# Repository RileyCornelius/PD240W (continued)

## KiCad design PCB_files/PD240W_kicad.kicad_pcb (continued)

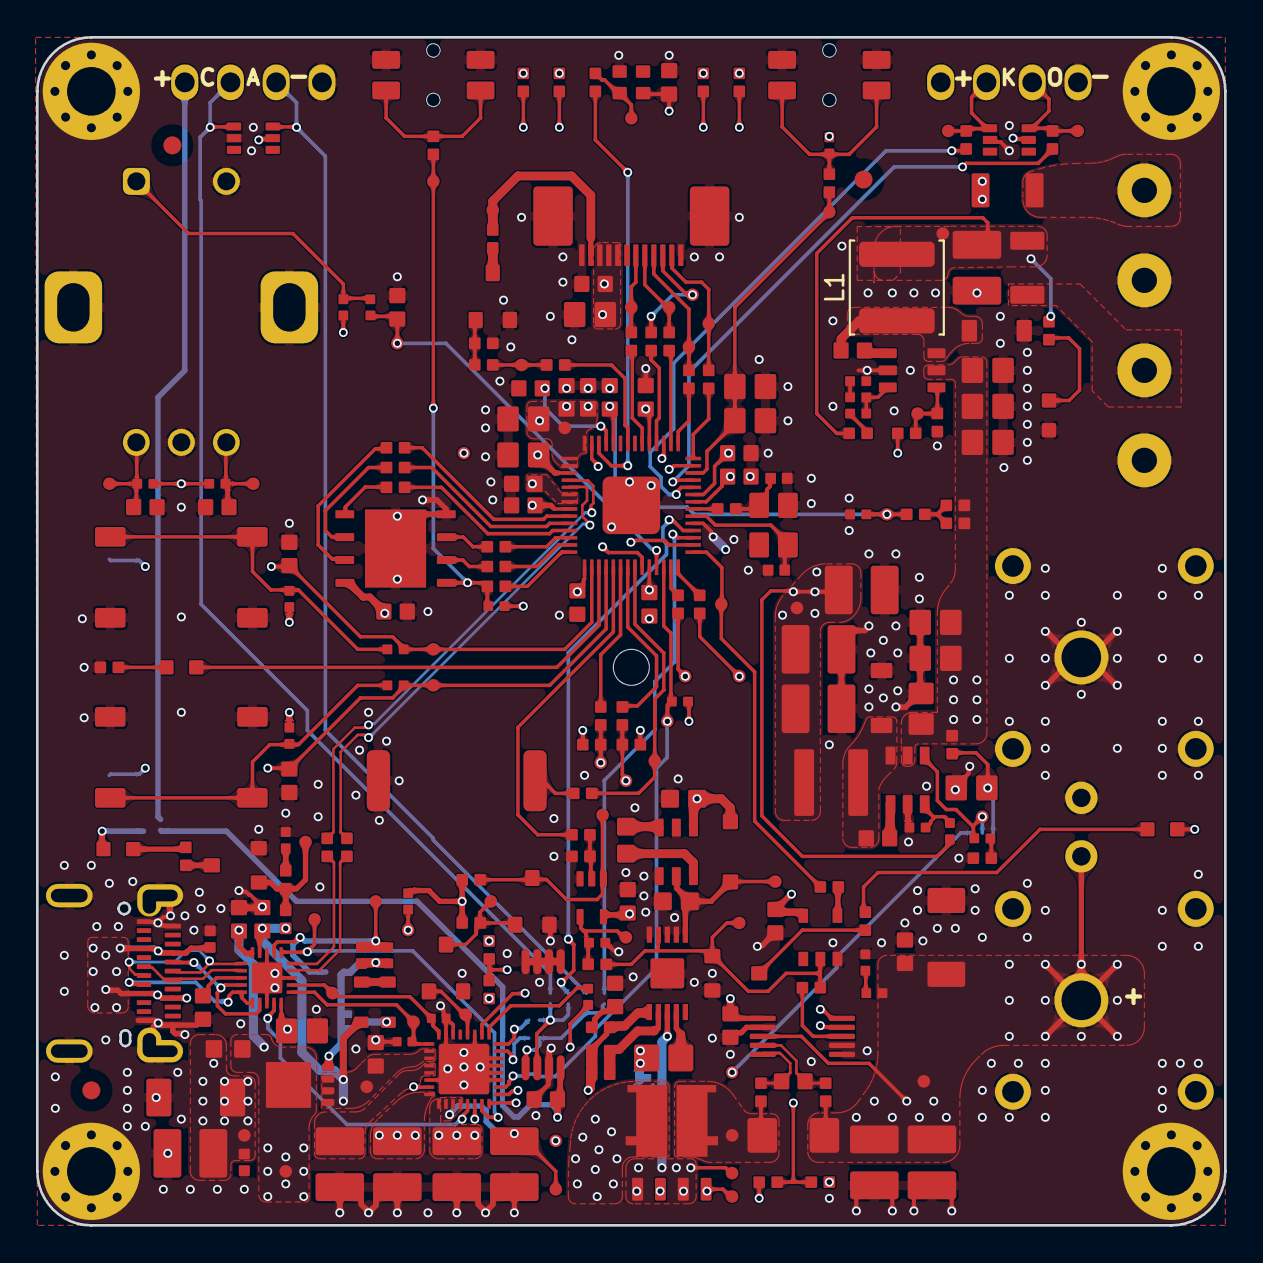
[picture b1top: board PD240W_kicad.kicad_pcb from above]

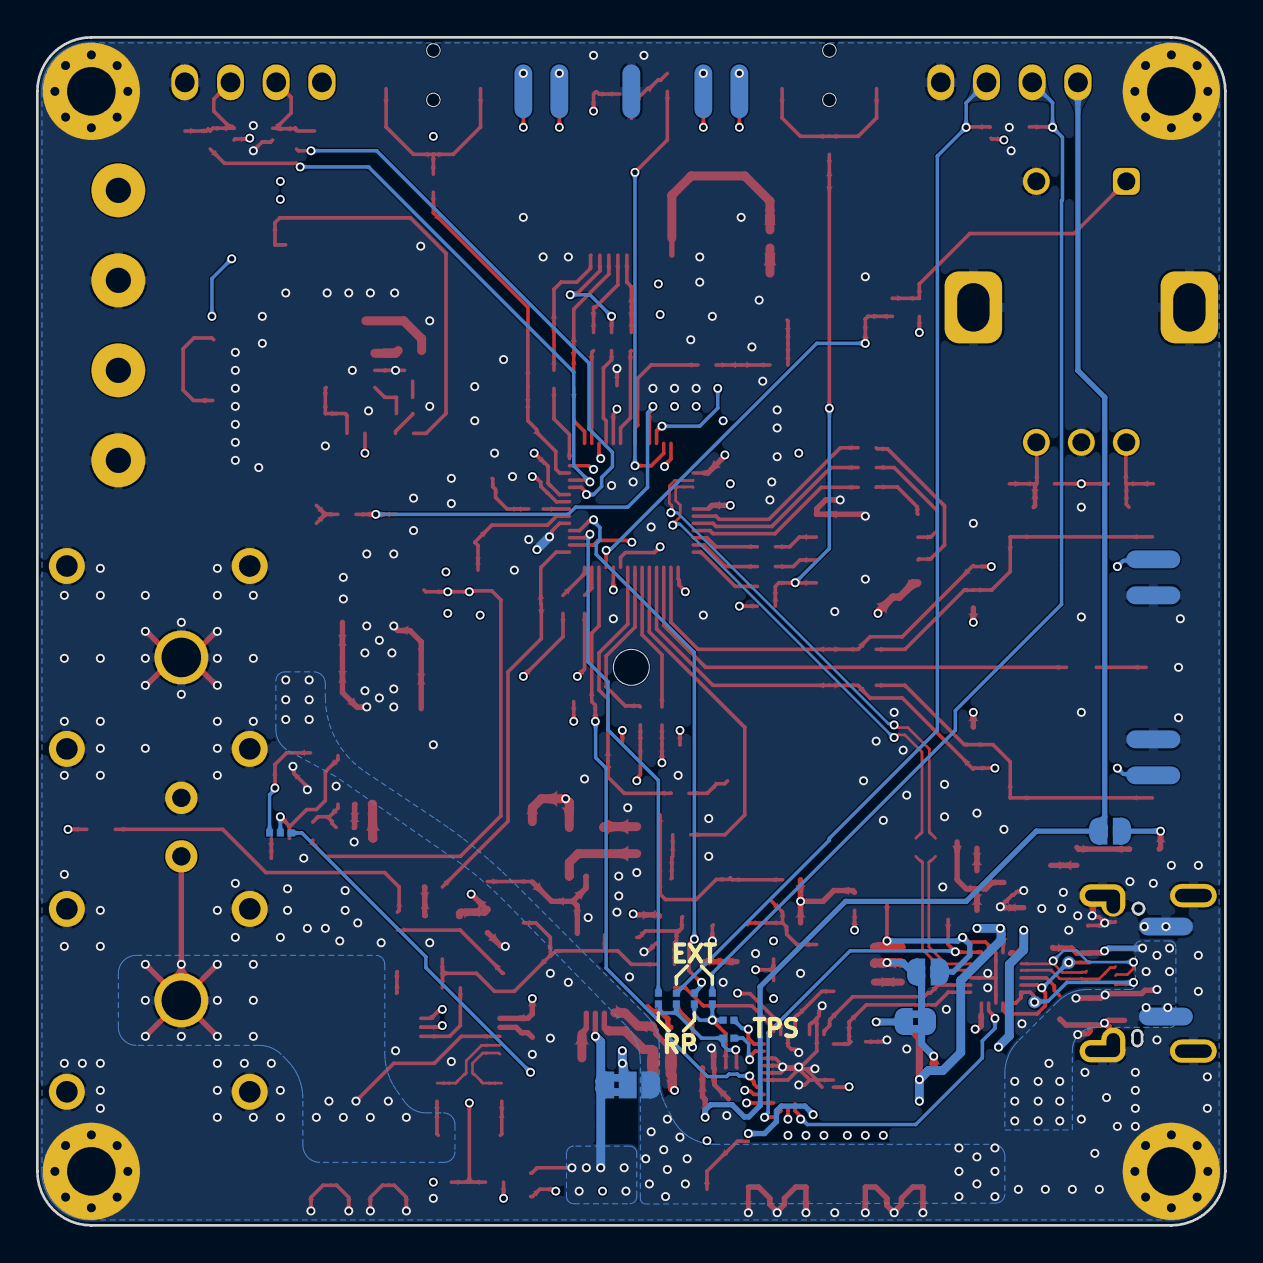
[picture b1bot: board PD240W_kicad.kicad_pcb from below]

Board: 6 copper layers, 66.0 x 66.0 mm, 299 parts (25 on the bottom side), 152 nets.

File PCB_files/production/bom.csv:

Designator,Footprint,Quantity,Value,LCSC Part #
"C1, C3, C7",capc_1005_06_n,3,10n X7R 100V,C527014
"C10, C16, C20, C21, C23, C24, C25, C26, C27, C30, C31, C38, C39, C4, C40, C41, C42, C43, C44, C45, C46, C47, C48, C49, C50, C51, C52, C54, C6, C62, C63, C8",capc_1608_09_l,32,100n X7R 100V,C15725
"C11, C13",capc_1005_06_l,2,220p X7R 50V,C296710
"C12, C14, C15, C28, C29, C65, C66, C67, C9",capc_3225_27_n,9,10u X7R 63V,C437568
"C17, C18, C19",capc_1608_09_n,3,3.3u X5R 25V,C5360803
"C2, C34, C35, C36, C37, C53, C55, C56, C57, C58, C59, C60, C61",capc_2012_14_n,13,1u X7R 100V,C5370002
C22,capc_2012_14_m,1,2.2u X7R 100V,C22367838
"C32, C33",capc_1005_06_n,2,15p COG 50V,C1548
C5,capc_3225_22_n,1,4.7u,C913445
C64,capc_3225_27_n,1,22u X7R 25V,C309062
"D1, D8",do-214ac_440p_430x250x230_n_p,2,SMAJ48A,C41376401
"D10, D14, D4, D7",kingbright_0603_blue,4,APTD1608LQBC/D,C5344742
D11,SK6812-EC20,1,SK6812-EC20,C2909058
"D12, D13",sod-123fl_305p_260x160x90_n,2,MBR1H100SFT3G,C235757
"D2, D3",sod-323_230p_170x125x100_n,2,BZT52C18SQ,C2857090
"D5, D9",sot363_sc88_65p_200x125x110_n,2,D3V3F4U6S-7,C1869321
D6,sod-123_270x155135_n,1,B0520LW-7-F,C155367
DSP1,generic_display_518x362x2_10mm_standoff,1,HS20HS072RX,C5329582
"F1, F2",ptc_1206_08_n,2,FSMD020-1206-R,C220145
FB1,fer_1608_09_n,1,BLM18SN220TH1D,C710392
J1,DX07S024JJ2R1300,1,DX07S024JJ2R1300,C2977282
J3,fcr7350r,1,24.245.1,C7437326
J4,fcr7350b,1,24.245.2,C7437327
"J5, J6",phoenix_1935776,2,1935776,C3817389
J8,AFC07-S12FCA-00,1,AFC07-S12FCA-00,C262559
L1,L_APV_ANR5020,1,33uH 1.3A 244mOhm,C9390
L2,SWPA4030S220MT,1,22uH 1A 0.29Ohm,C83472
PZ1,buzzer_9x9x2.1mm,1,FUET-9018,C391035
Q1,vsonp8_65p_330x330x80_mfg,1,AGM612AP,C5349119
"Q2, Q3, Q4, Q6, Q7",sot-23-3L_103p_300x130x110_n,5,AO3404A,C30010
Q5,PowerPAKSO-8_127p_513x615x120_n,1,SQJB90EP-T1_GE3,C727731
"R1, R33, R34, R5, R68, R74, R75, R82, R88",resc_1005_04_n,9,33k 1%,C138003
"R10, R11, R17, R26, R32, R7, R8, R83",resc_1005_04_m,8,4.7k 1%,C25900
"R12, R16, R2, R24, R35, R66, R69, R70, R72, R73, R76, R85, R86, R87, R89, R9",resc_1005_04_n,16,10k 1%,C25744
"R13, R14, R15, R19, R20, R22, R23, R25, R3, R4, R78, R80, R81, R84",resc_1005_04_m,14,100k 1%,C25741
"R18, R28, R30, R31, R37, R38, R39, R40, R41, R42, R43, R44, R45, R46, R48, R49, R50, R51, R52, R56, R57, R58, R59, R60, R61, R62, R63, R65, R77",resc_1005_04_m,29,27R 1%,C138021
"R21, R67, R71",resc_1005_04_m,3,330R 1%,C25104
R27,resc_1005_04_m,1,10k @25°C,C95939
R29,WSLP1206_n_current_sense_6m_to_50m,1,8m 1%,C2988654
"R36, R47, R53, R54, R55, R6, R64, R90",resc_1005_04_m,8,1k 1%,C11702
R79,resc_1005_04_m,1,3.9R 1%,C2933095
"S1, S2",EVQPUC02K,2,EVQ-PUC02K,C79174
"S3, S5",GT-TC120A-H120-L1,2,GT-TC120A-H120-L1,C2762973
S4,PEC11R-4215F-S0024,1,PEC11R-4215F-S0024,C143790
U1,wqfn20_40p_300x300x80_tp_170x170_n,1,TPD4S480RUKR,C43131250
U10,qfn56_40p_700x700x90_tp_320x320_mfg,1,RP2040,C2040
"U11, U12",sot6_p95_290x180x110_n,2,LMR16006XDDCR,C87080
U2,qfn32_40p_400x400x100_tp_280x280_mfg,1,TPS26750SRSMR,C42166327
U3,JEDEC_MO-153_AA,1,CAT24C512YI-GT3,C56096
U4,sot236_p95_290x160x110_n,1,LM2765,C140270
U5,sot353_65p_200x125x110_mo-203-aa_n,1,74LVC1G08SE-7,C460522
U6,msop_10p_300x490x110_tp168x188_n,1,LTC7004x,C690105
U7,vssop10_50p_300x300x110_mfg,1,INA228AIDGSR,C2887910
U8,sot25_95p_300x280x145_jedec_mo-178-aa_n,1,SN74LVC1G17DBVR,C7836
U9,wson8_127p_600x500x80_tp_435x340_n,1,W25Q128JVPIQ,C190862
Y1,osccc_320x205x80_abm8,1,ABM8-272-T3,C20625731

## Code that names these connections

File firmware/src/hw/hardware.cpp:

#include "hardware.h"
#include <Wire.h>
#include "platform/console.h"
#include "config/app_config.h"
#include "utils/logging.h"
#include "config/version.h"
#include "utils/tps_eeprom_loader.h"

Hardware hw;

Hardware::Hardware()
    : btn1(Board::PIN_BTN_1, ButtonPull::PULL_NONE, 10, true), btn2(Board::PIN_BTN_2, ButtonPull::PULL_NONE, 10, true),
      btnEnc(Board::PIN_ENC_BTN, ButtonPull::PULL_NONE, 50, true),
      overcurrentAlert(Board::PIN_SWITCH_EN_READ, IOMode::INPUT), pdInterrupt(Board::PIN_USB_PD_IRQ, IOMode::INPUT),
      encoder(Board::PIN_ENC_A, Board::PIN_ENC_B), buzzer(Board::PIN_BUZZER),
      rgbLed(Board::PIN_RGB_LED, pio0, Board::LED_IS_RGBW), en5v(Board::PIN_5V_EN, IOMode::OUTPUT),
      loadSwitch(Board::PIN_SWITCH_EN, IOMode::OUTPUT), pdController(&Wire, Board::I2C_ADDR_TPS26750),
      powerMonitor(&Wire, Board::I2C_ADDR_INA228, Board::INA228_SHUNT_RESISTOR, Board::INA228_MEASUREMENT_MAX_CURRENT,
                   Board::INA228_SHUNT_TEMPCO_PPM),
      display(spi0, Board::PIN_LCD_CS, Board::PIN_LCD_DC, Board::PIN_LCD_RST, Board::PIN_LCD_BL) {}

void Hardware::init() {
    // Short delay to let TPS26750 start up - actual PD negotiation is handled
    // adaptively during the boot screen via pdManager.waitForPdos()
    sleep_ms(50);
    Console::init();

    LOG_SEPARATOR();
    LOG_INFO("%s %s - %s", Version::PRODUCT_NAME, Version::PRODUCT_SUBTITLE, Version::FIRMWARE_VERSION);
    LOG_SEPARATOR();

    // =========================================================================
    // Communication Bus Init
    // =========================================================================

    // I2C0 (400kHz) - for INA228 and TPS26750. Under the Arduino core the two
    // driver libraries talk through Wire (== i2c0); the TPS patch loader still
    // uses raw SDK i2c0 calls on the same, now-initialized peripheral.
    Wire.setSDA(Board::PIN_I2C_SDA);
    Wire.setSCL(Board::PIN_I2C_SCL);
    Wire.setClock(Board::I2C_SPEED_HZ);
    Wire.begin();

    // SPI0 (10MHz) - for ST7789 display
    spi_init(spi0, Board::SPI_SPEED_HZ);
    spi_set_format(spi0, 8, SPI_CPOL_1, SPI_CPHA_1, SPI_MSB_FIRST);
    gpio_set_function(Board::PIN_LCD_SCK, GPIO_FUNC_SPI);
    gpio_set_function(Board::PIN_LCD_MOSI, GPIO_FUNC_SPI);

    // =========================================================================
    // Peripheral Driver Init
    // =========================================================================

    // Simple drivers (no external communication)
    encoder.init();
    buzzer.init();
    LOG_HW_INIT("ADC", adc.init());

    // Display (SPI)
    LOG_HW_INIT("ST7789 Display", display.init());

    // I2C devices
    if (pdController.init()) {
        LOG_INFO("TPS26750 PD Controller initialized successfully with FW %s", Version::TPS_FIRMWARE_VERSION);
    } else {
        LOG_ERROR("TPS26750 PD Controller initialization FAILED");
    }
    _power_monitor_ok = powerMonitor.init();
    if (_power_monitor_ok) {
        if (!powerMonitor.setADCRange(Board::INA228_USE_LOW_ADC_RANGE)) {
            LOG_WARN("INA228 ADC range configuration failed");
        }
        LOG_INFO("INA228 Power monitor initialized successfully with FW %s", Version::INA_FIRMWARE_VERSION);
    } else {
        LOG_ERROR("INA228 Power monitor initialization FAILED - load switch disabled "
                  "(no current sensing / overcurrent protection)");
    }

    // RGB LED (PIO)
    LOG_HW_INIT("SK6812 RGB LED", rgbLed.init());

    // =========================================================================
    // Initial Output States
    // =========================================================================
    loadSwitch.off();
    rgbLed.setColor(LedColor::BLUE, AppConfig::RGB_LED_BRIGHTNESS_NORMAL);
}

void Hardware::update() {
    // Update drivers that need periodic polling
    rgbLed.update();
}
